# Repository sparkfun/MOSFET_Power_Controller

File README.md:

MOSFET Power Controller
=======================

[  
*MOSFET Power Controller(PRT-11214)*](https://www.sparkfun.com/products/11214)

This MOSFET Power Controller board allows you to turn a high current battery power supply on and off via microcontroller inputs. 

Repository Contents
-------------------
* **/Hardware** - All Eagle design files (.brd, .sch)
* **/Production** - Test bed files and production panel files

License Information
-------------------
The hardware is released under [Creative Commons Share-alike 3.0](http://creativecommons.org/licenses/by-sa/3.0/).

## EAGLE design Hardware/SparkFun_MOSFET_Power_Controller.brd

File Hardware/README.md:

# What Are these Files?

The .sch and .brd files hare are Eagle CAD schematic and PCB design files.

These files were created with Eagle 6.3.0, you'll need Eagle 6.3 or later to open them up. There is a free, lite, version of Eagle available from [cadsoftusa.com](cadsoftusa.com).

# License

This product is open source! These Eagle files are released under the Creative Commons Share-Alike Attribution license ([CC BY-SA 3.0](http://creativecommons.org/licenses/by-sa/3.0/us/)).

Please use, reuse, and modify these files as you see fit. Please maintain attribution and release anything derivative under the same license.

- Your friends at SparkFun.

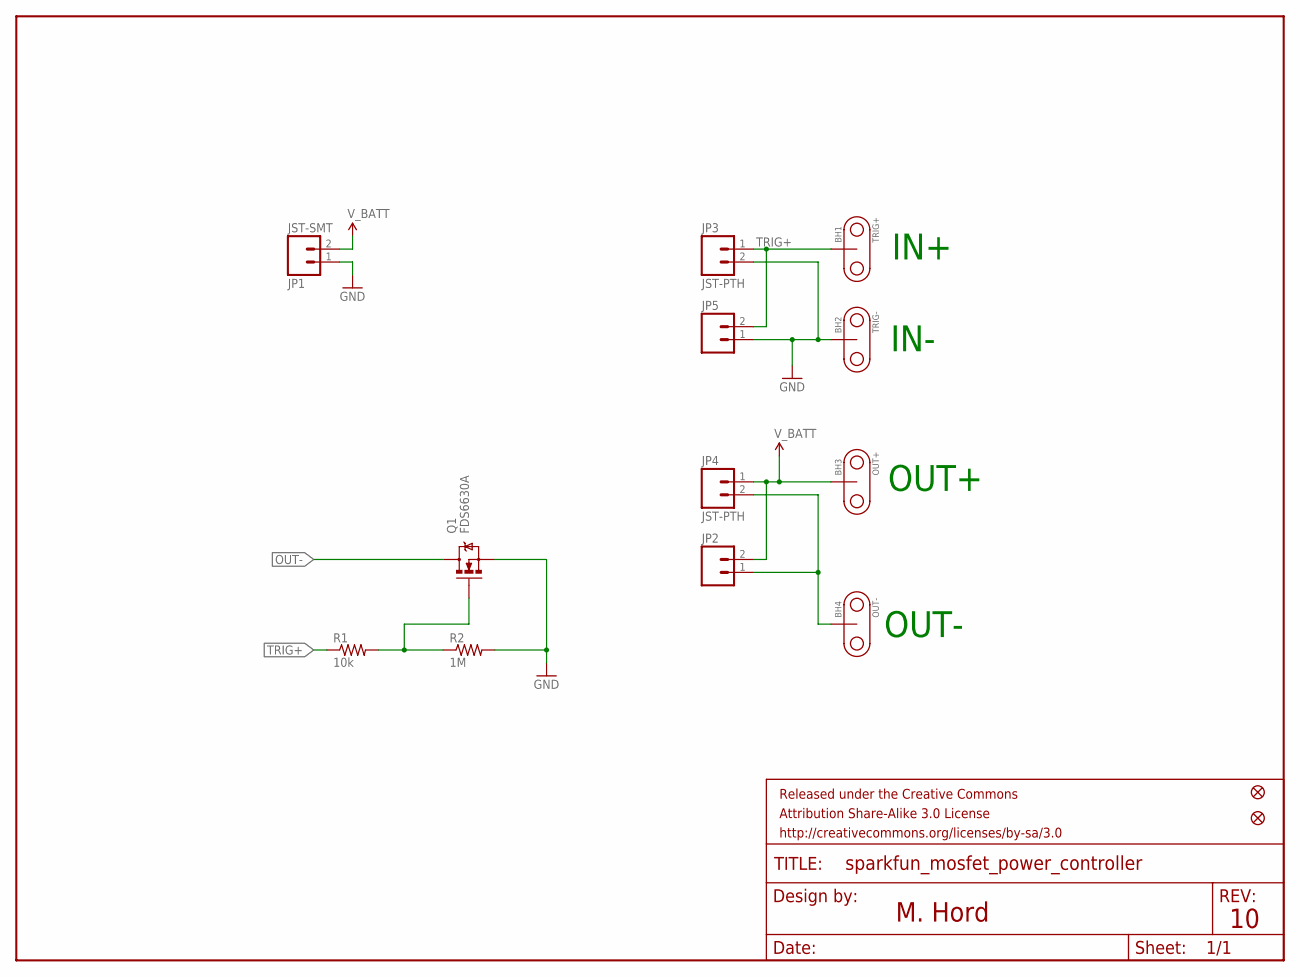
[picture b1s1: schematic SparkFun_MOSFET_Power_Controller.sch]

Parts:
BH1: TRIG+; BUTTONHOLE
BH2: TRIG-; BUTTONHOLE
BH3: OUT+; BUTTONHOLE
BH4: OUT-; BUTTONHOLE
FRAME1: FRAME-LETTER; CREATIVE_COMMONS
JP1: JST-SMT; JST-2-SMD
JP2, JP5: M02PTH; 1X02
JP3, JP4: JST-PTH; JST-2-PTH-NS
JP6, JP7: FIDUCIALUFIDUCIAL; MICRO-FIDUCIAL
Q1: FDS6630A; SO08
R1: 10k; 0402-RES
R2: 1M; 0402-RES

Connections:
GND: BH2.P$1, JP1.1 (2), JP3.2, JP5.1, Q1.1 (S), Q1.2 (S), Q1.3 (S), R2.2
unnamed: Q1.4 (G), R1.2, R2.1
OUT-: BH4.P$1, JP2.1, JP4.2, Q1.5 (D), Q1.6 (D), Q1.7 (D), Q1.8 (D)
TRIG+: BH1.P$1, JP3.1, JP5.2, R1.1
V_BATT: BH3.P$1, JP1.2 (1), JP2.2, JP4.1

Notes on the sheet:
M. Hord
IN+
IN-
OUT+
OUT-

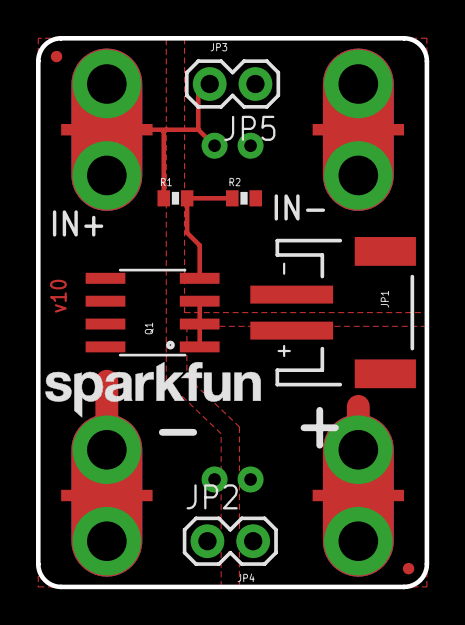
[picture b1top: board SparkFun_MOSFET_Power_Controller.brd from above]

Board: 2 copper layers, 21.6 x 30.5 mm, 15 parts (0 on the bottom side), 5 nets.

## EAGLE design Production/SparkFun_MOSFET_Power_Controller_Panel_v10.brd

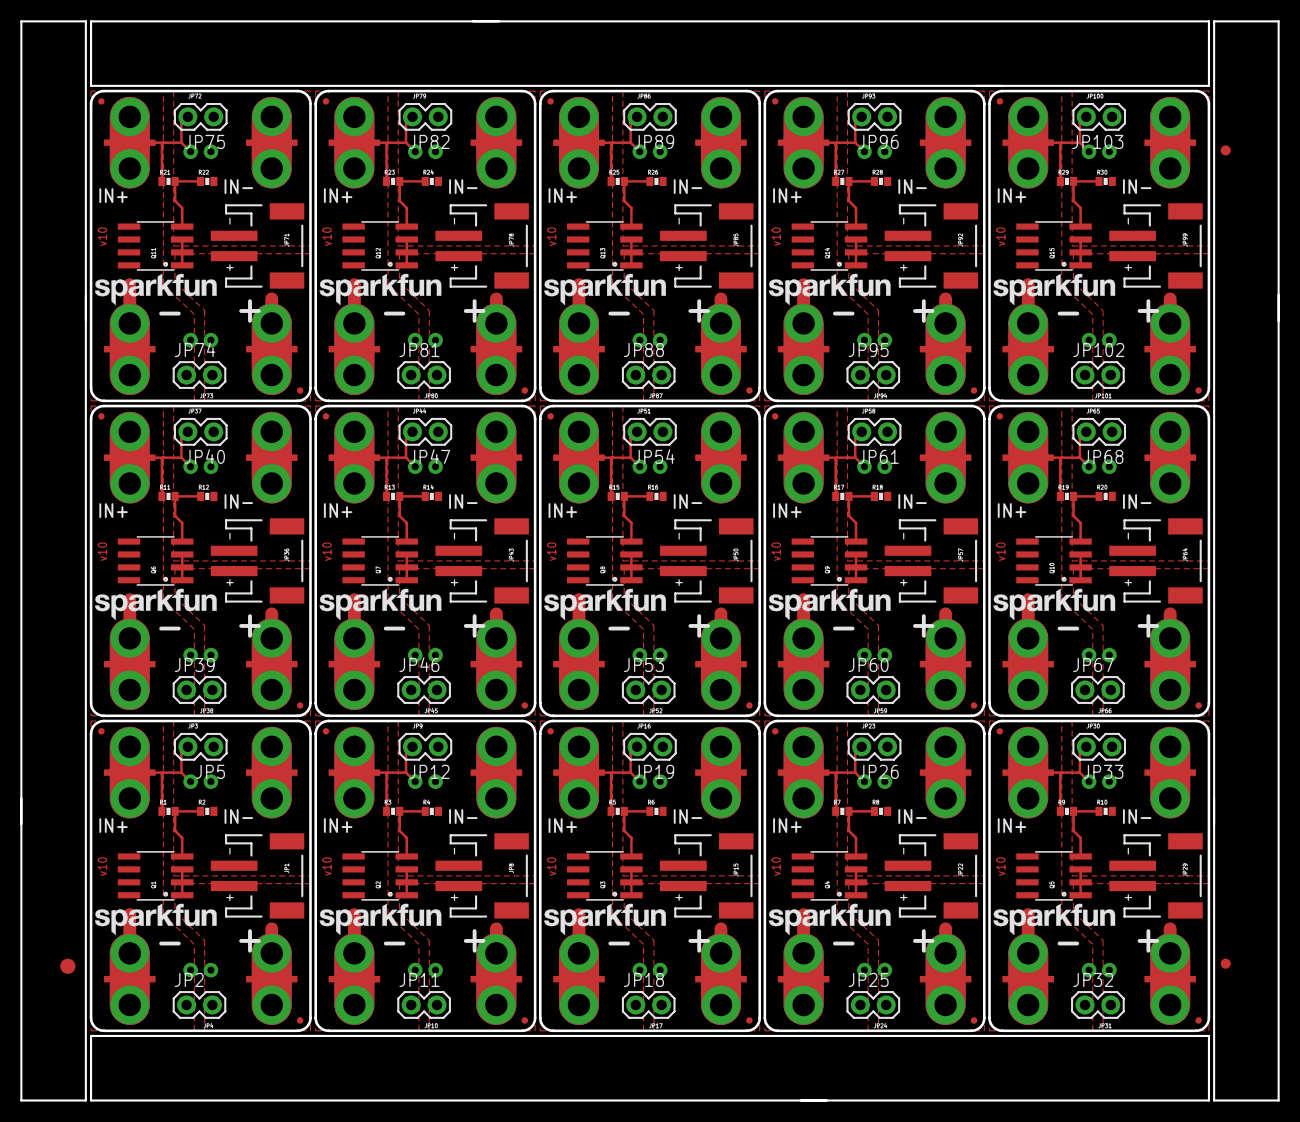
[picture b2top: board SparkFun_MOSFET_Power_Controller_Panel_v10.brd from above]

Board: 2 copper layers, 123.7 x 106.2 mm, 213 parts (0 on the bottom side), 75 nets.

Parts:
BH1, BH5, BH9, BH13, BH17, BH21, BH25, BH29, BH33, BH37, BH41, BH45, BH49, BH53, BH57: TRIG+; BUTTONHOLE
BH2, BH6, BH10, BH14, BH18, BH22, BH26, BH30, BH34, BH38, BH42, BH46, BH50, BH54, BH58: TRIG-; BUTTONHOLE
BH3, BH7, BH11, BH15, BH19, BH23, BH27, BH31, BH35, BH39, BH43, BH47, BH51, BH55, BH59: OUT+; BUTTONHOLE
BH4, BH8, BH12, BH16, BH20, BH24, BH28, BH32, BH36, BH40, BH44, BH48, BH52, BH56, BH60: OUT-; BUTTONHOLE
E$1: FIDUCIAL-1.5X3
E$5, E$6: FIDUCIAL-1X2
JP1, JP8, JP15, JP22, JP29, JP36, JP43, JP50, JP57, JP64, JP71, JP78, JP85, JP92, JP99: JST-SMT; JST-2-SMD
JP2, JP5, JP11, JP12, JP18, JP19, JP25, JP26, JP32, JP33, JP39, JP40, JP46, JP47, JP53, JP54, JP60, JP61, JP67, JP68, JP74, JP75, JP81, JP82, JP88, JP89, JP95, JP96, JP102, JP103: 1X02
JP3, JP4, JP9, JP10, JP16, JP17, JP23, JP24, JP30, JP31, JP37, JP38, JP44, JP45, JP51, JP52, JP58, JP59, JP65, JP66, JP72, JP73, JP79, JP80, JP86, JP87, JP93, JP94, JP100, JP101: JST-PTH; JST-2-PTH-NS
JP6, JP7, JP13, JP14, JP20, JP21, JP27, JP28, JP34, JP35, JP41, JP42, JP48, JP49, JP55, JP56, JP62, JP63, JP69, JP70, JP76, JP77, JP83, JP84, JP90, JP91, JP97, JP98, JP104, JP105: FIDUCIALUFIDUCIAL; MICRO-FIDUCIAL
Q1, Q2, Q3, Q4, Q5, Q6, Q7, Q8, Q9, Q10, Q11, Q12, Q13, Q14, Q15: FDS6630A; SO08
R1, R3, R5, R7, R9, R11, R13, R15, R17, R19, R21, R23, R25, R27, R29: 10k; 0402-RES
R2, R4, R6, R8, R10, R12, R14, R16, R18, R20, R22, R24, R26, R28, R30: 1M; 0402-RES

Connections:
GND: BH2.P$1, JP1.1, JP3.2, JP5.1, Q1.1, Q1.2, Q1.3, R2.2
GND1: BH6.P$1, JP8.1, JP9.2, JP12.1, Q2.1, Q2.2, Q2.3, R4.2
GND2: BH10.P$1, JP15.1, JP16.2, JP19.1, Q3.1, Q3.2, Q3.3, R6.2
GND3: BH14.P$1, JP22.1, JP23.2, JP26.1, Q4.1, Q4.2, Q4.3, R8.2
GND4: BH18.P$1, JP29.1, JP30.2, JP33.1, Q5.1, Q5.2, Q5.3, R10.2
GND5: BH22.P$1, JP36.1, JP37.2, JP40.1, Q6.1, Q6.2, Q6.3, R12.2
GND6: BH26.P$1, JP43.1, JP44.2, JP47.1, Q7.1, Q7.2, Q7.3, R14.2
GND7: BH30.P$1, JP50.1, JP51.2, JP54.1, Q8.1, Q8.2, Q8.3, R16.2
GND8: BH34.P$1, JP57.1, JP58.2, JP61.1, Q9.1, Q9.2, Q9.3, R18.2
GND9: BH38.P$1, JP64.1, JP65.2, JP68.1, Q10.1, Q10.2, Q10.3, R20.2
GND10: BH42.P$1, JP71.1, JP72.2, JP75.1, Q11.1, Q11.2, Q11.3, R22.2
GND11: BH46.P$1, JP78.1, JP79.2, JP82.1, Q12.1, Q12.2, Q12.3, R24.2
GND12: BH50.P$1, JP85.1, JP86.2, JP89.1, Q13.1, Q13.2, Q13.3, R26.2
GND13: BH54.P$1, JP92.1, JP93.2, JP96.1, Q14.1, Q14.2, Q14.3, R28.2
GND14: BH58.P$1, JP99.1, JP100.2, JP103.1, Q15.1, Q15.2, Q15.3, R30.2
unnamed: Q1.4, R1.2, R2.1
unnamed: Q2.4, R3.2, R4.1
unnamed: Q3.4, R5.2, R6.1
unnamed: Q4.4, R7.2, R8.1
unnamed: Q5.4, R9.2, R10.1
unnamed: Q6.4, R11.2, R12.1
unnamed: Q7.4, R13.2, R14.1
unnamed: Q8.4, R15.2, R16.1
unnamed: Q9.4, R17.2, R18.1
unnamed: Q10.4, R19.2, R20.1
unnamed: Q11.4, R21.2, R22.1
unnamed: Q12.4, R23.2, R24.1
unnamed: Q13.4, R25.2, R26.1
unnamed: Q14.4, R27.2, R28.1
unnamed: Q15.4, R29.2, R30.1
OUT-: BH4.P$1, JP2.1, JP4.2, Q1.5, Q1.6, Q1.7, Q1.8
OUT-1: BH8.P$1, JP10.2, JP11.1, Q2.5, Q2.6, Q2.7, Q2.8
OUT-2: BH12.P$1, JP17.2, JP18.1, Q3.5, Q3.6, Q3.7, Q3.8
OUT-3: BH16.P$1, JP24.2, JP25.1, Q4.5, Q4.6, Q4.7, Q4.8
OUT-4: BH20.P$1, JP31.2, JP32.1, Q5.5, Q5.6, Q5.7, Q5.8
OUT-5: BH24.P$1, JP38.2, JP39.1, Q6.5, Q6.6, Q6.7, Q6.8
OUT-6: BH28.P$1, JP45.2, JP46.1, Q7.5, Q7.6, Q7.7, Q7.8
OUT-7: BH32.P$1, JP52.2, JP53.1, Q8.5, Q8.6, Q8.7, Q8.8
OUT-8: BH36.P$1, JP59.2, JP60.1, Q9.5, Q9.6, Q9.7, Q9.8
OUT-9: BH40.P$1, JP66.2, JP67.1, Q10.5, Q10.6, Q10.7, Q10.8
OUT-10: BH44.P$1, JP73.2, JP74.1, Q11.5, Q11.6, Q11.7, Q11.8
OUT-11: BH48.P$1, JP80.2, JP81.1, Q12.5, Q12.6, Q12.7, Q12.8
OUT-12: BH52.P$1, JP87.2, JP88.1, Q13.5, Q13.6, Q13.7, Q13.8
OUT-13: BH56.P$1, JP94.2, JP95.1, Q14.5, Q14.6, Q14.7, Q14.8
OUT-14: BH60.P$1, JP101.2, JP102.1, Q15.5, Q15.6, Q15.7, Q15.8
TRIG+: BH1.P$1, JP3.1, JP5.2, R1.1
TRIG+1: BH5.P$1, JP9.1, JP12.2, R3.1
TRIG+2: BH9.P$1, JP16.1, JP19.2, R5.1
TRIG+3: BH13.P$1, JP23.1, JP26.2, R7.1
TRIG+4: BH17.P$1, JP30.1, JP33.2, R9.1
TRIG+5: BH21.P$1, JP37.1, JP40.2, R11.1
TRIG+6: BH25.P$1, JP44.1, JP47.2, R13.1
TRIG+7: BH29.P$1, JP51.1, JP54.2, R15.1
TRIG+8: BH33.P$1, JP58.1, JP61.2, R17.1
TRIG+9: BH37.P$1, JP65.1, JP68.2, R19.1
TRIG+10: BH41.P$1, JP72.1, JP75.2, R21.1
TRIG+11: BH45.P$1, JP79.1, JP82.2, R23.1
TRIG+12: BH49.P$1, JP86.1, JP89.2, R25.1
TRIG+13: BH53.P$1, JP93.1, JP96.2, R27.1
TRIG+14: BH57.P$1, JP100.1, JP103.2, R29.1
V_BATT: BH3.P$1, JP1.2, JP2.2, JP4.1
V_BATT1: BH7.P$1, JP8.2, JP10.1, JP11.2
V_BATT2: BH11.P$1, JP15.2, JP17.1, JP18.2
V_BATT3: BH15.P$1, JP22.2, JP24.1, JP25.2
V_BATT4: BH19.P$1, JP29.2, JP31.1, JP32.2
V_BATT5: BH23.P$1, JP36.2, JP38.1, JP39.2
V_BATT6: BH27.P$1, JP43.2, JP45.1, JP46.2
V_BATT7: BH31.P$1, JP50.2, JP52.1, JP53.2
V_BATT8: BH35.P$1, JP57.2, JP59.1, JP60.2
V_BATT9: BH39.P$1, JP64.2, JP66.1, JP67.2
V_BATT10: BH43.P$1, JP71.2, JP73.1, JP74.2
V_BATT11: BH47.P$1, JP78.2, JP80.1, JP81.2
V_BATT12: BH51.P$1, JP85.2, JP87.1, JP88.2
V_BATT13: BH55.P$1, JP92.2, JP94.1, JP95.2
V_BATT14: BH59.P$1, JP99.2, JP101.1, JP102.2

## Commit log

2013-01-22 Initial commit- these are v02 files, as run in the last prototype phase.
2013-01-28 Swap source and drain pins.
    The original schematic symbol isn't clear on which pins are drain
    and which are source, so I screwed it up. The MOSFET was always
    conducting through the body diode.
    This version fixes it and should be considered for release.
2013-02-25 RedBoard release v10 Rotate MOSFET 180 degrees. Fixed flame on silk overlapping MOSFET. Added .1" headers at either end.
2013-02-28 Production readied
    added fiducial reference points and created panel for manufacture
2013-04-22 Update repo structure and add a README with licensing.
2015-05-06 Updating file names, adding gitattributes
2015-12-23 created new v10 panel
2025-06-27 Update README.md
    Updating link

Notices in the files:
parts and their libraries:
SparkFun-Aesthetics: Licensing: CC v3.0 Share-Alike You are welcome to use this library for commercial purposes.
SparkFun-Aesthetics: Released under the Creative Commons Attribution Share-Alike 3.0 License
